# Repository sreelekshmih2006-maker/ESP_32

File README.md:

# ESP32 4-Layer Development Board

## Overview

This project is a custom 4-layer ESP32 development board designed in KiCad using the official Espressif ESP32-DevKitC V4 reference design as the foundation. The objective was to understand professional PCB design practices, including schematic capture, component placement, signal routing, power distribution, and multilayer PCB stack-up.

## Features

* ESP32-WROOM-32 module
* 4-layer PCB design
* USB-UART programming interface (CP2102)
* AMS1117-3.3 voltage regulator
* EN and BOOT buttons
* USB connector for programming and power
* Standard GPIO pin headers
* Ground and power planes for improved signal integrity

## PCB Stack-up

* **F.Cu** – Signal routing and components
* **In1.Cu** – Solid Ground Plane
* **In2.Cu** – 3.3 V Power Plane
* **B.Cu** – Signal routing and components

## Design Process

1. Created the schematic using KiCad.
2. Verified the design with Electrical Rules Check (ERC).
3. Assigned footprints to all components.
4. Imported the schematic into the PCB Editor.
5. Designed a 4-layer PCB with dedicated ground and power planes.
6. Routed signals while maintaining ESP32 antenna keep-out requirements.
7. Verified the PCB using Design Rules Check (DRC).
8. Generated Gerber and drill files for manufacturing.

## Main Components

* ESP32-WROOM-32
* CP2102 USB-to-UART Bridge
* AMS1117-3.3 Voltage Regulator
* USB Connector
* Push Buttons (EN and BOOT)
* LEDs
* Resistors and Capacitors
* Pin Headers

## Software Used

* KiCad 10
* Git
* GitHub

## Project Files

* Schematic (.kicad_sch)
* PCB Layout (.kicad_pcb)
* Gerber Files
* Drill Files

## References

* Espressif ESP32-DevKitC V4 Reference Design
* KiCad Official Documentation

## Author

**Sreelekshmi H**
First-Year Electronics and Communication Engineering Student
Cochin University of Science and Technology (CUSAT)

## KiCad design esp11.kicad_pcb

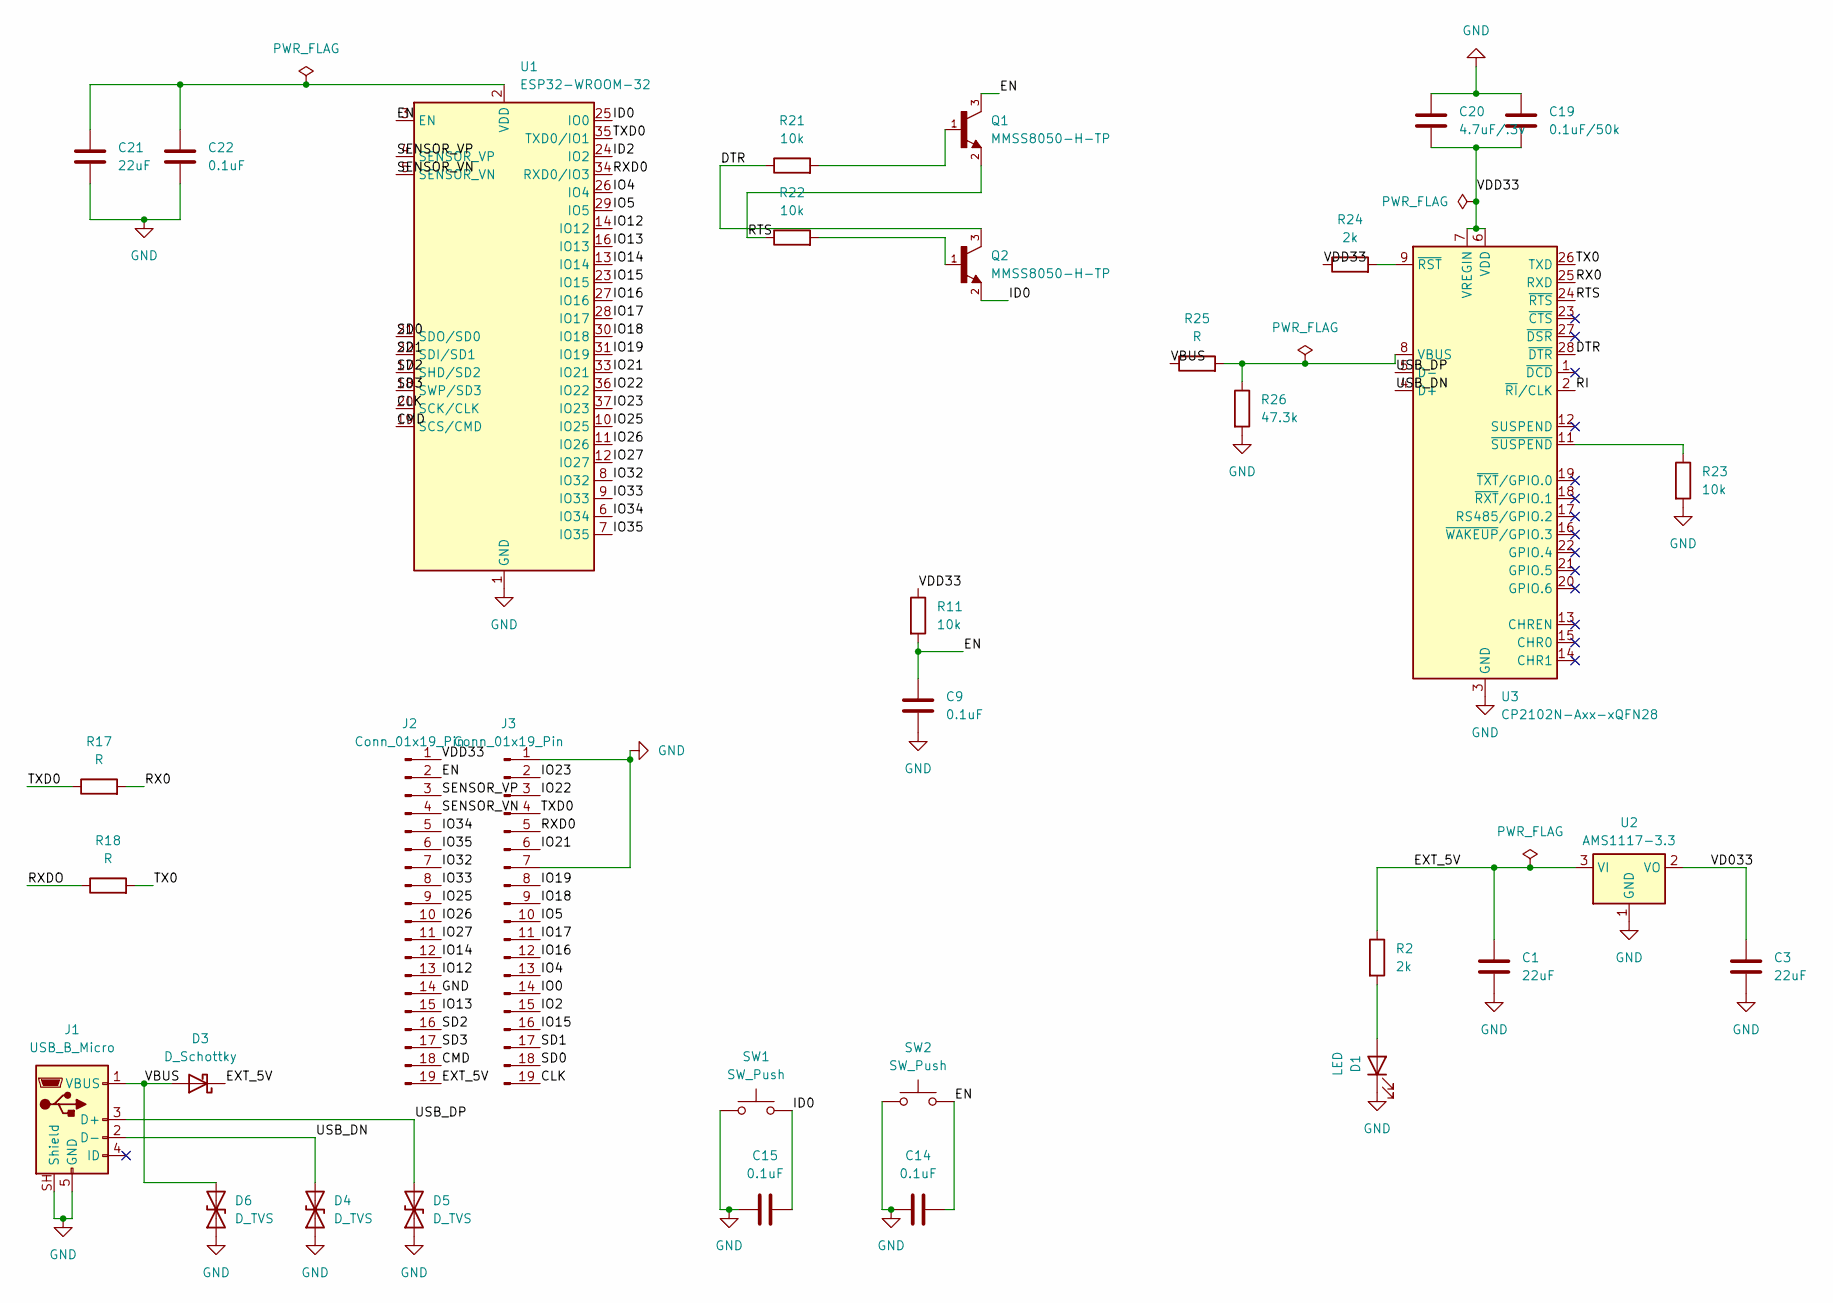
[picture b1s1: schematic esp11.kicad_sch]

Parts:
C1, C3, C21: 22uF; C_0603_1608Metric
C9, C14, C15, C22: 0.1uF; C_0603_1608Metric
C19: 0.1uF/50k; C_0603_1608Metric
C20: 4.7uF/.3v; C_0603_1608Metric
D1: LED; LED_0603_1608Metric
D3: D_Schottky; D_SOD-323
D4, D5, D6: D_TVS; D_SOD-523
J1: USB_B_Micro; USB_Micro-AB_Molex_47590-0001
J2, J3: Conn_01x19_Pin; PinHeader_1x19_P2.54mm_Vertical
Q1, Q2: MMSS8050-H-TP; TRANS_MMSS8050-H-TP; PARTREV D
R2, R24: 2k; R_0603_1608Metric
R11, R21, R22, R23: 10k; R_0603_1608Metric
R17, R18, R25: R; R_0603_1608Metric
R26: 47.3k; R_0603_1608Metric
SW1, SW2: SW_Push; SW_SPST_B3S-1000
U1: ESP32-WROOM-32
U2: AMS1117-3.3; SOT-223-3_TabPin2
U3: CP2102N-Axx-xQFN28; QFN-28-1EP_5x5mm_P0.5mm_EP3.35x3.35mm

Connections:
/CLK: J3.19, U1.20 (SCK/CLK)
/CMD: J2.18, U1.19 (SCS/CMD)
/DTR: Q2.3, R21.1, U3.28 (~DTR)
/EN: C9.1, C14.2, J2.2, Q1.3, R11.2, SW2.2, U1.3 (EN)
/EXT_5V: C1.1, D3.1 (K), J2.19, R2.1, U2.3 (VI)
/ID0: C15.2, Q2.2, SW1.2, U1.25 (IO0)
/ID2: U1.24 (IO2)
/IO0: J3.14
/IO2: J3.15
/IO4: J3.13, U1.26 (IO4)
/IO5: J3.10, U1.29 (IO5)
/IO12: J2.13, U1.14 (IO12)
/IO13: J2.15, U1.16 (IO13)
/IO14: J2.12, U1.13 (IO14)
/IO15: J3.16, U1.23 (IO15)
/IO16: J3.12, U1.27 (IO16)
/IO17: J3.11, U1.28 (IO17)
/IO18: J3.9, U1.30 (IO18)
/IO19: J3.8, U1.31 (IO19)
/IO21: J3.6, U1.33 (IO21)
/IO22: J3.3, U1.36 (IO22)
/IO23: J3.2, U1.37 (IO23)
/IO25: J2.9, U1.10 (IO25)
/IO26: J2.10, U1.11 (IO26)
/IO27: J2.11, U1.12 (IO27)
/IO32: J2.7, U1.8 (IO32)
/IO33: J2.8, U1.9 (IO33)
/IO34: J2.5, U1.6 (IO34)
/IO35: J2.6, U1.7 (IO35)
/RI: U3.2 (~RI/CLK)
/RTS: Q1.2, R22.1, U3.24 (~RTS)
/RX0: R17.2, U3.25 (RXD)
/RXD0: J3.5, U1.34 (RXD0/IO3)
/RXDO: R18.1
/SD0: J3.18, U1.21 (SDO/SD0)
/SD2: J2.16, U1.17 (SHD/SD2)
/SD3: J2.17, U1.18 (SWP/SD3)
/SENSOR_VN: J2.4, U1.5 (SENSOR_VN)
/SENSOR_VP: J2.3, U1.4 (SENSOR_VP)
/TX0: R18.2, U3.26 (TXD)
/TXD0: J3.4, R17.1, U1.35 (TXD0/IO1)
/USB_DN: D4.2 (A2), J1.2 (D-), U3.4 (D+)
/USB_DP: D5.2 (A2), J1.3 (D+), U3.5 (D-)
/VBUS: D3.2 (A), D6.2 (A2), J1.1 (VBUS), R25.1
/VD033: C3.1, U2.2 (VO)
/VDD33: C19.2, C20.2, J2.1, R11.1, R24.1, U3.6 (VDD), U3.7 (VREGIN)
unnamed: D1.2 (A), R2.2
unnamed: Q1.1, R21.2
unnamed: Q2.1, R22.2
unnamed: C21.1, C22.1, U1.2 (VDD)
unnamed: R25.2, R26.1, U3.8 (VBUS)
unnamed: R24.2, U3.9 (~RST)
unnamed: R23.1, U3.11 (~SUSPEND)

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
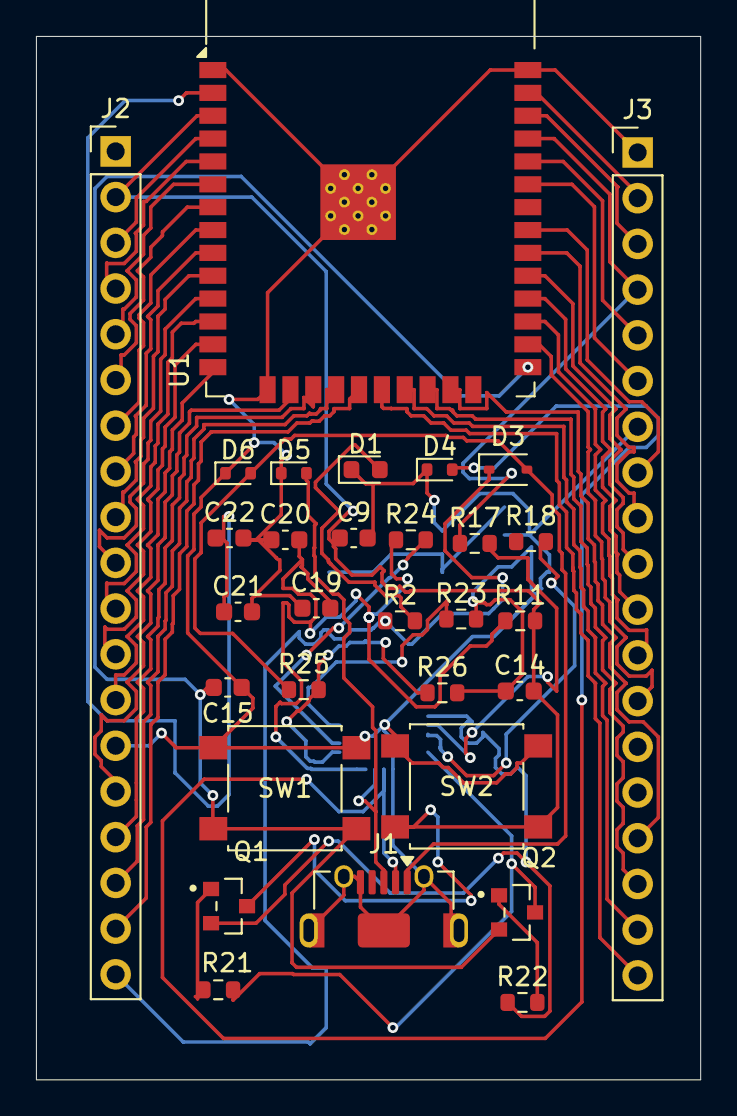
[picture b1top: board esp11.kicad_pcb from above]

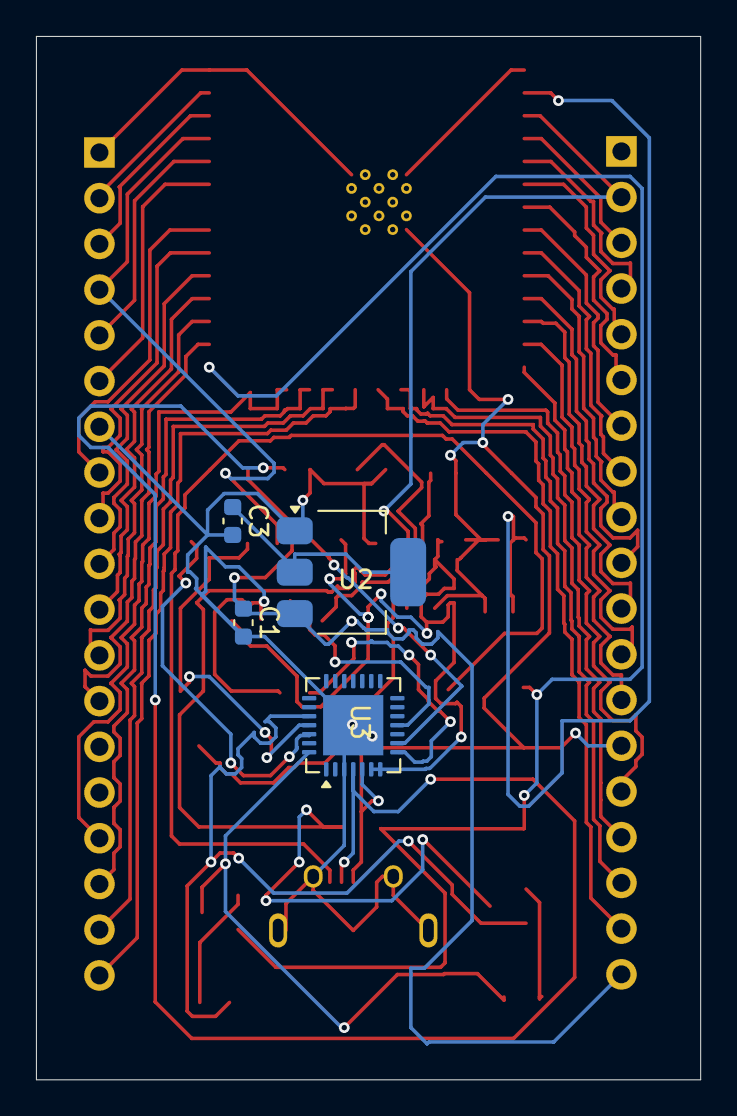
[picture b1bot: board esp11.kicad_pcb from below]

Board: 4 copper layers, 36.9 x 58.0 mm, 34 parts (4 on the bottom side), 50 nets.

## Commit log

2026-06-30 Fixed commit
2026-06-30 Add Gerber files
2026-06-30 Add README for ESP32 4-layer development board
    Added detailed project overview, features, design process, and components for the ESP32 4-layer development board.
